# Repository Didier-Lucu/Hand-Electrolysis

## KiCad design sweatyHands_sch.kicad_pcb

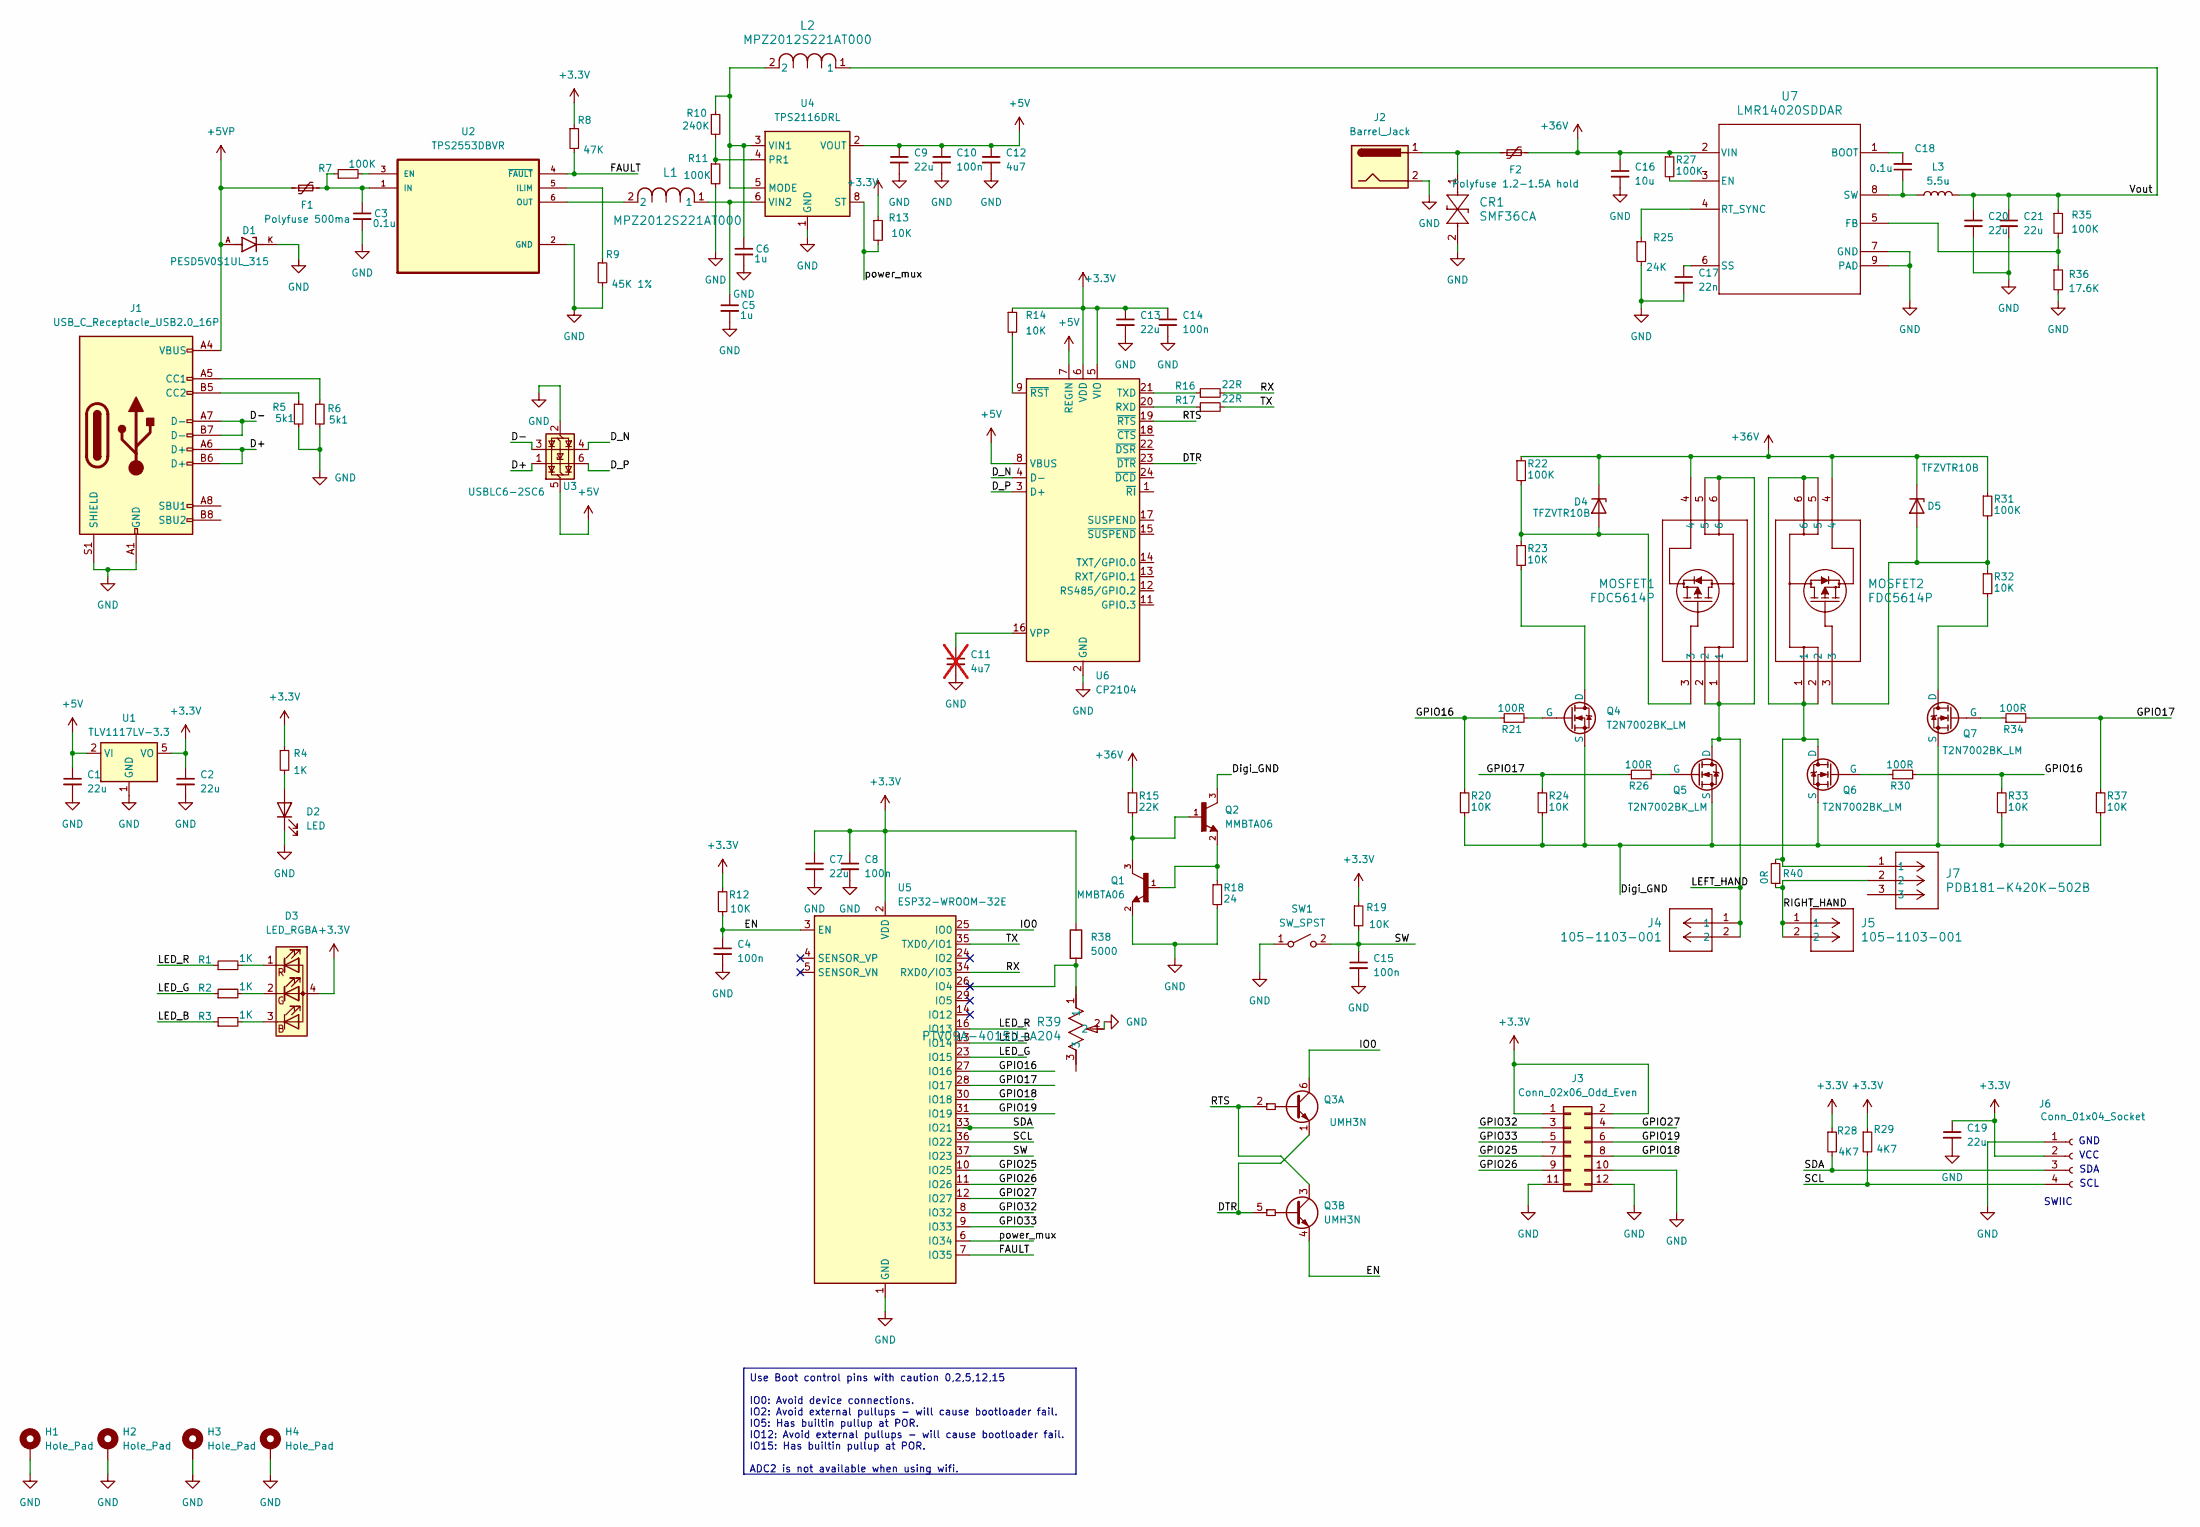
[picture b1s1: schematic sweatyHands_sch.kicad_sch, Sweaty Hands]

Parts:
C1, C2, C7, C9, C13, C20, C21: 22u; C_0603_1608Metric_Pad1.08x0.95mm_HandSolder
C3: 0.1u; C_0603_1608Metric_Pad1.08x0.95mm_HandSolder
C4, C8, C10, C14, C15: 100n; C_0603_1608Metric_Pad1.08x0.95mm_HandSolder
C5, C6: 1u; C_0603_1608Metric_Pad1.08x0.95mm_HandSolder
C11: 4u7; C_0805_2012Metric_Pad1.18x1.45mm_HandSolder; not fitted
C12: 4u7; C_0603_1608Metric_Pad1.08x0.95mm_HandSolder
C16: 10u; C_0603_1608Metric_Pad1.08x0.95mm_HandSolder
C17: 22n; C_0603_1608Metric_Pad1.08x0.95mm_HandSolder
C18: 0.1u; R_0603_1608Metric_Pad0.98x0.95mm_HandSolder
C19: 22u; C_0805_2012Metric_Pad1.18x1.45mm_HandSolder
CR1: SMF36CA; SOD-123F_LTF
D1: PESD5V0S1UL_315; DIO_PESD5V0S1UL_315; PARTREV 15 January 2020
D2: LED; LED_0603_1608Metric_Pad1.05x0.95mm_HandSolder
D3: LED_RGBA; LED_RGB_Wuerth-PLCC4_3.2x2.8mm_150141M173100
D4, D5: TFZVTR10B; DIO_TDZVT_ROM-M
F1: Polyfuse 500ma; Fuse_0805_2012Metric_Pad1.15x1.40mm_HandSolder
F2: Polyfuse 1.2-1.5A hold; Fuse_0805_2012Metric_Pad1.15x1.40mm_HandSolder
H1, H2, H3, H4: Hole_Pad; MountingHole_3.2mm_M3_Pad_Via
J1: USB_C_Receptacle_USB2.0_16P; USB_C_Receptacle_Amphenol_12401948E412A
J2: Barrel_Jack; CUI_PJ-002B
J3: Conn_02x06_Odd_Even; PinHeader_2x06_P2.54mm_Vertical
J4, J5: 105-1103-001; CONN_105-1102-001
J6: Conn_01x04_Socket; PinHeader_1x04_P2.54mm_Vertical
J7: PDB181-K420K-502B; CONN3_PDB181-K420K-502B_BRN
L1, L2: MPZ2012S221AT000; IND_2012_TDK
L3: 5.5u; L_0805_2012Metric
MOSFET1, MOSFET2: FDC5614P; TSOT23-6_419BL_ONS
Q1, Q2: MMBTA06; TRANS_MMBTA06; PARTREV 1.1.0; DigiKey_Part_Number 4878-MMBTA06CT-ND
Q3: UMH3N; SOT-363_SC-70-6
Q4, Q5, Q6, Q7: T2N7002BK_LM; SOT23_TOS-M
R1, R2, R3, R4: 1K; R_0603_1608Metric_Pad0.98x0.95mm_HandSolder
R5, R6: 5k1; R_0603_1608Metric_Pad0.98x0.95mm_HandSolder
R7, R11, R22, R27, R31, R35: 100K; R_0603_1608Metric_Pad0.98x0.95mm_HandSolder
R8: 47K; R_0603_1608Metric_Pad0.98x0.95mm_HandSolder
R9: 45K 1%; R_0603_1608Metric_Pad0.98x0.95mm_HandSolder
R10: 240K; R_0603_1608Metric_Pad0.98x0.95mm_HandSolder
R12, R13, R19, R20, R23, R24, R32, R33, R37: 10K; R_0603_1608Metric_Pad0.98x0.95mm_HandSolder
R14: 10K; R_0201_0603Metric_Pad0.64x0.40mm_HandSolder
R15: 22K; R_0603_1608Metric_Pad0.98x0.95mm_HandSolder
R16, R17: 22R; R_0603_1608Metric_Pad0.98x0.95mm_HandSolder
R18: 24; R_0603_1608Metric_Pad0.98x0.95mm_HandSolder
R21, R26, R30, R34: 100R; R_0603_1608Metric_Pad0.98x0.95mm_HandSolder
R25: 24K; R_0603_1608Metric_Pad0.98x0.95mm_HandSolder
R28, R29: 4K7; R_0603_1608Metric_Pad0.98x0.95mm_HandSolder
R36: 17.6K; R_0603_1608Metric_Pad0.98x0.95mm_HandSolder
R38: 5000; R_0603_1608Metric_Pad0.98x0.95mm_HandSolder
R39: PTV09A-4015U-A204; POT_PTV09A-4x15x-xxxx_BRN
R40: 0R; R_0603_1608Metric_Pad0.98x0.95mm_HandSolder
SW1: SW_SPST; SW_Push_1TS009xxxx-xxxx-xxxx_6x6x5mm
U1: TLV1117LV-3.3; WSON-8-1EP_4x4mm_P0.8mm_EP2.2x3mm
U2: TPS2553DBVR; SOT95P280X145-6N
U3: USBLC6-2SC6; SOT-23-6
U4: TPS2116DRL; SOT-583-8
U5: ESP32-WROOM-32E; ESP32-WROOM-32D
U6: CP2104; QFN-24-1EP_4x4mm_P0.5mm_EP2.6x2.6mm
U7: LMR14020SDDAR; DDA0008E_N

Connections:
+5V: C1.1, C9.1, C10.1, C12.1, U1.2 (VI), U1.3 (VI), U1.4 (VI), U3.5 (VBUS), U4.2 (VOUT), U4.7 (VOUT), U6.7 (REGIN), U6.8 (VBUS)
+5VP: D1.A, F1.1, J1.A4 (VBUS), J1.A9 (VBUS), J1.B4 (VBUS), J1.B9 (VBUS)
+36V: C16.1, D4.1 (K), D5.1 (K), F2.2, MOSFET1.4, MOSFET2.4, R15.1, R22.1, R27.1, R31.1, U7.2 (VIN)
/D+: J1.A6 (D+), J1.B6 (D+), U3.1 (I/O1)
/D-: J1.A7 (D-), J1.B7 (D-), U3.3 (I/O2)
/DTR: Q3.1 (E1), Q3.5 (B2), U6.23 (~DTR)
/D_N: U3.4 (I/O2), U6.4 (D-)
/D_P: U3.6 (I/O1), U6.3 (D+)
/Digi_GND: Q2.3, Q4.3 (S), Q5.3 (S), Q6.3 (S), Q7.3 (S), R20.2, R24.2, R33.2, R37.2
/EN: C4.1, Q3.4 (E2), R12.2, U5.3 (EN)
/FAULT: R8.2, U2.4 (~FAULT), U5.7 (IO35)
/GPIO16: R20.1, R21.1, R30.2, R33.1, U5.27 (IO16)
/GPIO17: R24.1, R26.1, R34.2, R37.1, U5.28 (IO17)
/GPIO18: J3.8, U5.30 (IO18)
/GPIO19: J3.6, U5.31 (IO19)
/GPIO25: J3.7, U5.10 (IO25)
/GPIO26: J3.9, U5.11 (IO26)
/GPIO27: J3.4, U5.12 (IO27)
/GPIO32: J3.3, U5.8 (IO32)
/GPIO33: J3.5, U5.9 (IO33)
/IO0: Q3.6 (C1), U5.25 (IO0)
/LED_B: R3.1, U5.13 (IO14)
/LED_G: R2.1, U5.23 (IO15)
/LED_R: R1.1, U5.16 (IO13)
/LEFT_HAND: J4.1, J4.2, MOSFET1.1, MOSFET1.2, MOSFET1.5, MOSFET1.6, Q5.1 (D)
/RIGHT_HAND: J5.1, J5.2, J7.2, R40.1
/RTS: Q3.2 (B1), Q3.3 (C2), U6.19 (~RTS)
/RX: R16.2, U5.34 (RXD0/IO3)
/SCL: J6.4, R29.2, U5.36 (IO22)
/SDA: J6.3, R28.2, U5.33 (IO21)
/SW: C15.1, R19.2, SW1.2 (B), U5.37 (IO23)
/TX: R17.2, U5.35 (TXD0/IO1)
/Vout: C20.1, C21.1, L2.1, L3.2, R35.1
/power_mux: R13.2, U4.8 (ST), U5.6 (IO34)
unnamed: CR1.1, F2.1, J2.1
unnamed: D2.2 (A), R4.2
unnamed: D3.3 (BK), R3.2
unnamed: D3.2 (GK), R2.2
unnamed: D3.1 (RK), R1.2
unnamed: D4.2 (A), MOSFET1.3, R22.2, R23.1
unnamed: D5.2 (A), MOSFET2.3, R31.2, R32.1
unnamed: J1.A5 (CC1), R6.1
unnamed: J1.B5 (CC2), R5.1
unnamed: Q1.1, Q2.2, R18.1
unnamed: Q1.3, Q2.1, R15.2
unnamed: Q4.1 (D), R23.2
unnamed: Q4.2 (G), R21.2
unnamed: Q5.2 (G), R26.2
unnamed: J7.1, MOSFET2.1, MOSFET2.2, MOSFET2.5, MOSFET2.6, Q6.1 (D), R40.2
unnamed: Q6.2 (G), R30.1
unnamed: Q7.1 (D), R32.2
unnamed: Q7.2 (G), R34.1
unnamed: R7.2, U2.3 (EN)
unnamed: R9.1, U2.5 (ILIM)
unnamed: C3.1, F1.2, R7.1, U2.1 (IN)
unnamed: L1.2, U2.6 (OUT)
unnamed: C6.1, L2.2, R10.1, U4.3 (VIN1), U4.5 (MODE)
unnamed: R10.2, R11.1, U4.4 (PR1)
unnamed: C5.1, L1.1, U4.6 (VIN2)
unnamed: R17.1, U6.20 (RXD)
unnamed: R16.1, U6.21 (TXD)
unnamed: C11.1, U6.16 (VPP)
unnamed: R14.2, U6.9 (~RST)
unnamed: C18.2, U7.1 (BOOT)
unnamed: R27.2, U7.3 (EN)
unnamed: R35.2, R36.1, U7.5 (FB)
unnamed: R25.1, U7.4 (RT_SYNC)
unnamed: C17.1, U7.6 (SS)
unnamed: C18.1, L3.1, U7.8 (SW)

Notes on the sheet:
GND
SDA
VCC
SWIIC
SCL
Use Boot control pins with caution 0,2,5,12,15 IO0: Avoid device connections. IO2: Avoid external pullups - will cause bootloader fail. IO5: Has builtin pullup at POR. IO12: Avoid external pullups - will cause bootloader fail. IO15: Has builtin pullup at POR. ADC2 is not available when using wifi.

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
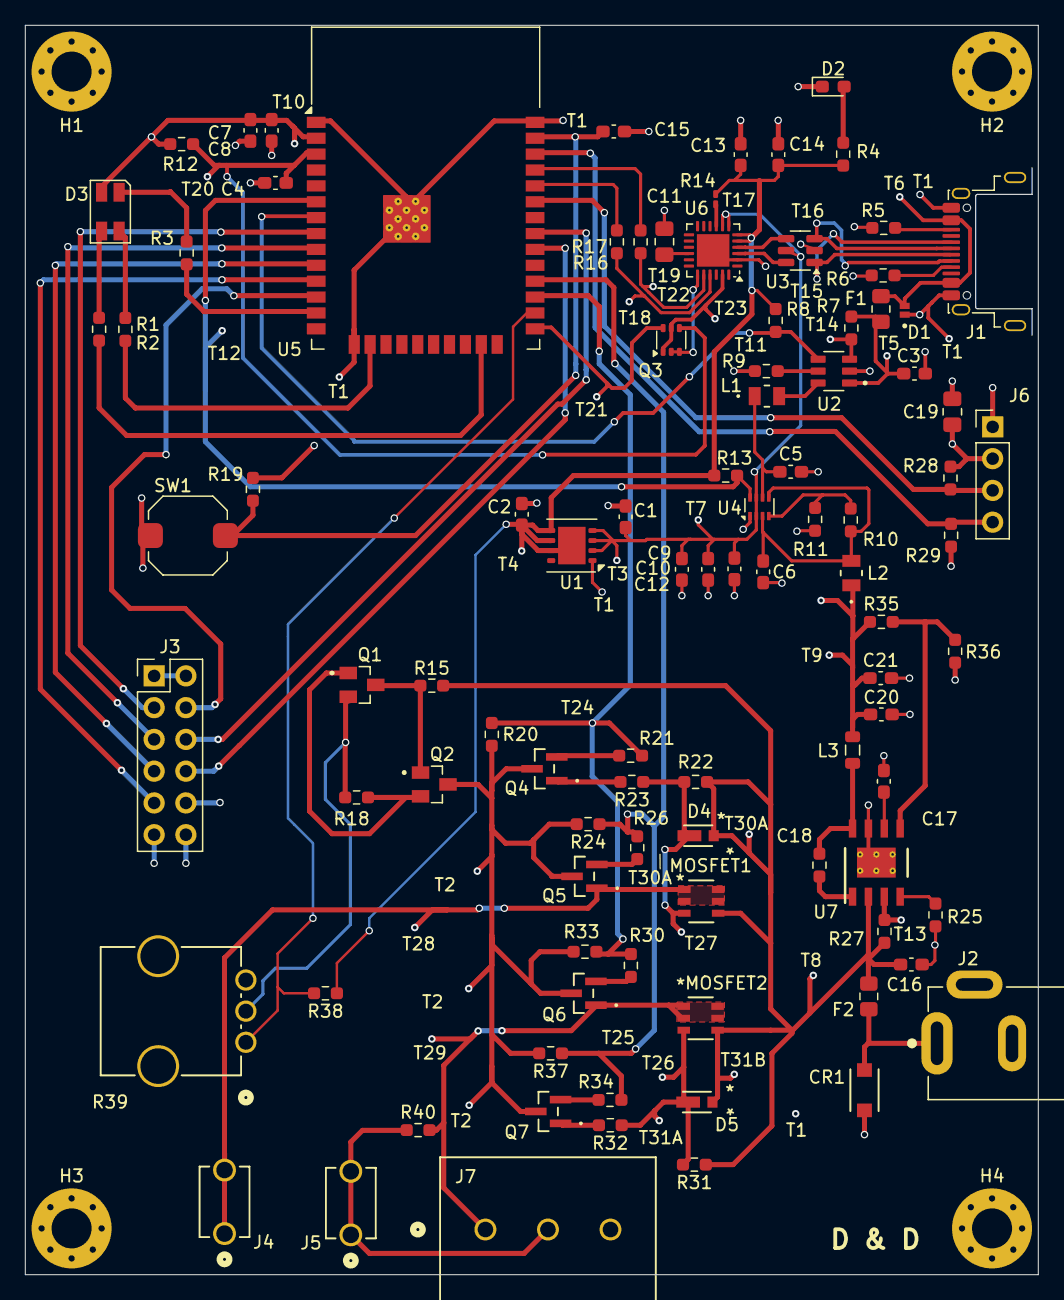
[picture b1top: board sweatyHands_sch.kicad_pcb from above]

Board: 4 copper layers, 81.0 x 99.8 mm, 100 parts (0 on the bottom side), 71 nets.

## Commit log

2025-08-08 Start of MCU
2025-08-08 Finished power and MCU
2025-08-09 Added Duel Power
2025-08-12 Almost done with Hbridge
2025-08-12 Finished Schem
2025-09-04 Meow
2025-09-09 ABout halfway done with PCB
2025-09-12 First Complete Draft done
2025-09-18 Finished PCB
